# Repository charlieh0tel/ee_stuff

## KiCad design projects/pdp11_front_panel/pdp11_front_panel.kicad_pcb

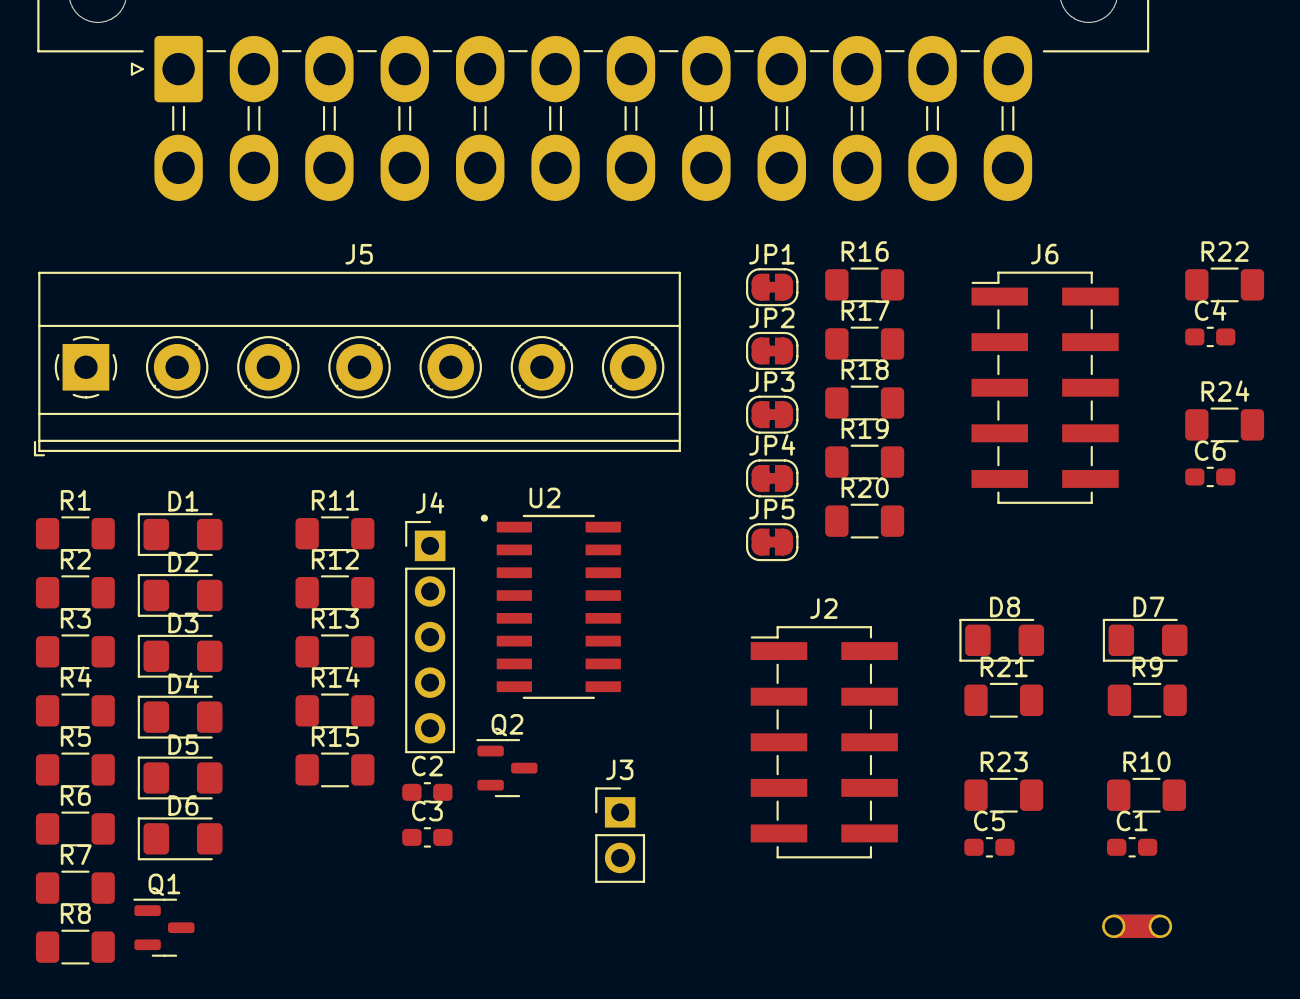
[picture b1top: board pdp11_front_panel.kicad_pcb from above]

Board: 2 copper layers, 53 parts (0 on the bottom side), 35 nets, no tracks yet.

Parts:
C1, C3, C4, C5, C6: 1u; C_0603_1608Metric_Pad1.08x0.95mm_HandSolder
C2: 0.01u; C_0603_1608Metric_Pad1.08x0.95mm_HandSolder
D1, D2, D3, D4, D5, D6, D7, D8: LED; LED_1206_3216Metric_Pad1.42x1.75mm_HandSolder
J1: ATX-24; Molex_Mini-Fit_Jr_5569-24A1_2x12_P4.20mm_Horizontal
J2, J6: Conn_02x05_Odd_Even; PinHeader_2x05_P2.54mm_Vertical_SMD
J3: Conn_01x02; PinHeader_1x02_P2.54mm_Vertical
J4: Conn_01x05_Pin; PinHeader_1x05_P2.54mm_Vertical
J5: Screw_Terminal_01x07; TerminalBlock_Phoenix_MKDS-1,5-7-5.08_1x07_P5.08mm_Horizont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
JP1, JP2, JP3, JP4, JP5: SolderJumper_2_Bridged; SolderJumper-2_P1.3mm_Bridged_RoundedPad1.0x1.5mm
NT1: NetTie_2; NetTie-2_THT_Pad1.0mm
Q1, Q2: 2N7002; SOT-23
R1, R12, R13, R14: 22; R_1206_3216Metric_Pad1.30x1.75mm_HandSolder
R2, R15: 100K; R_1206_3216Metric_Pad1.30x1.75mm_HandSolder
R3, R4, R5, R6, R7, R8: R; R_1206_3216Metric_Pad1.30x1.75mm_HandSolder
R9, R21: 1K; R_1206_3216Metric_Pad1.30x1.75mm_HandSolder
R10, R11, R22, R23, R24: 10K; R_1206_3216Metric_Pad1.30x1.75mm_HandSolder
R16, R17, R18, R19, R20: 2K; R_1206_3216Metric_Pad1.30x1.75mm_HandSolder
U2: AM26S10CDRG4; SOIC127P600X175-16N

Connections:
+5VA: C2.1, C3.1, NT1.2, R11.1, R16.2, R17.2, R18.2, R19.2, R20.2, U2.16 (VCC)
/+3V3: J1.1 (+3.3V), J1.2 (+3.3V), J1.12 (+3.3V), J1.13 (+3.3V), R7.1
/+5V: J1.4 (+5V), J1.6 (+5V), J1.21 (+5V), J1.22 (+5V), J1.23 (+5V), J5.1, J5.2, R8.1
/+5VSB: J1.9 (+5VSB), NT1.1, R3.1, R4.1
/+12V: J1.10 (+12V), J1.11 (+12V), J5.3, J5.4, R6.1
/-12V: J1.14 (-12V), J5.5, R5.1
/BDCOK_H: J2.10, J6.10, JP3.2 (B), U2.7 (2B)
/BEVNT_L: J2.2, J6.2, JP4.2 (B), U2.2 (1B)
/BHALT_L: J2.9, J6.9, JP2.2 (B), U2.9 (3B)
/BPOK_H: J2.1, J6.1, JP1.2 (B), U2.15 (4B)
/Controller/60HZ/50HZ#: J3.2, R11.2
/Controller/SW_AUX: C5.1, R23.2
/Controller/SW_PWR: C1.1, R10.2
/Controller/SW_RESTART#: C4.1, R22.2
/Controller/SW_RUN/HALT#: C6.1, R24.2
/PS_ON#: J1.16 (PS_ON#), Q2.3 (D)
/PWR_OK: J1.8 (PWR_OK), R1.1, R12.1
/SRUN_L: J2.3, J6.3, JP5.2 (B), R13.2
GND: C1.2, C2.2, C3.2, C4.2, C5.2, C6.2, D2.1 (K), D3.2 (A), D4.1 (K), D5.1 (K), D6.1 (K), D7.1 (K), D8.1 (K), J1.3 (GND), J1.5 (GND), J1.7 (GND), J1.15 (GND), J1.17 (GND), J1.18 (GND), J1.19 (GND), J1.24 (GND), J2.5, J3.1, J4.1, J5.6, J5.7, J6.5, Q1.2 (S), Q2.2 (S), R2.2, R15.2, U2.1 (GND), U2.8 (GND)
unnamed: D1.2 (A), R3.2
unnamed: D1.1 (K), Q1.3 (D)
unnamed: D2.2 (A), R4.2
unnamed: D3.1 (K), R5.2
unnamed: D4.2 (A), R6.2
unnamed: D5.2 (A), R7.2
unnamed: D6.2 (A), R8.2
unnamed: D7.2 (A), R9.2
unnamed: D8.2 (A), R21.2
unnamed: JP1.1 (A), R16.1
unnamed: JP2.1 (A), R17.1
unnamed: JP3.1 (A), R18.1
unnamed: JP4.1 (A), R19.1
unnamed: JP5.1 (A), R20.1
unnamed: Q1.1 (G), R1.2, R2.1
unnamed: Q2.1 (G), R14.2, R15.1

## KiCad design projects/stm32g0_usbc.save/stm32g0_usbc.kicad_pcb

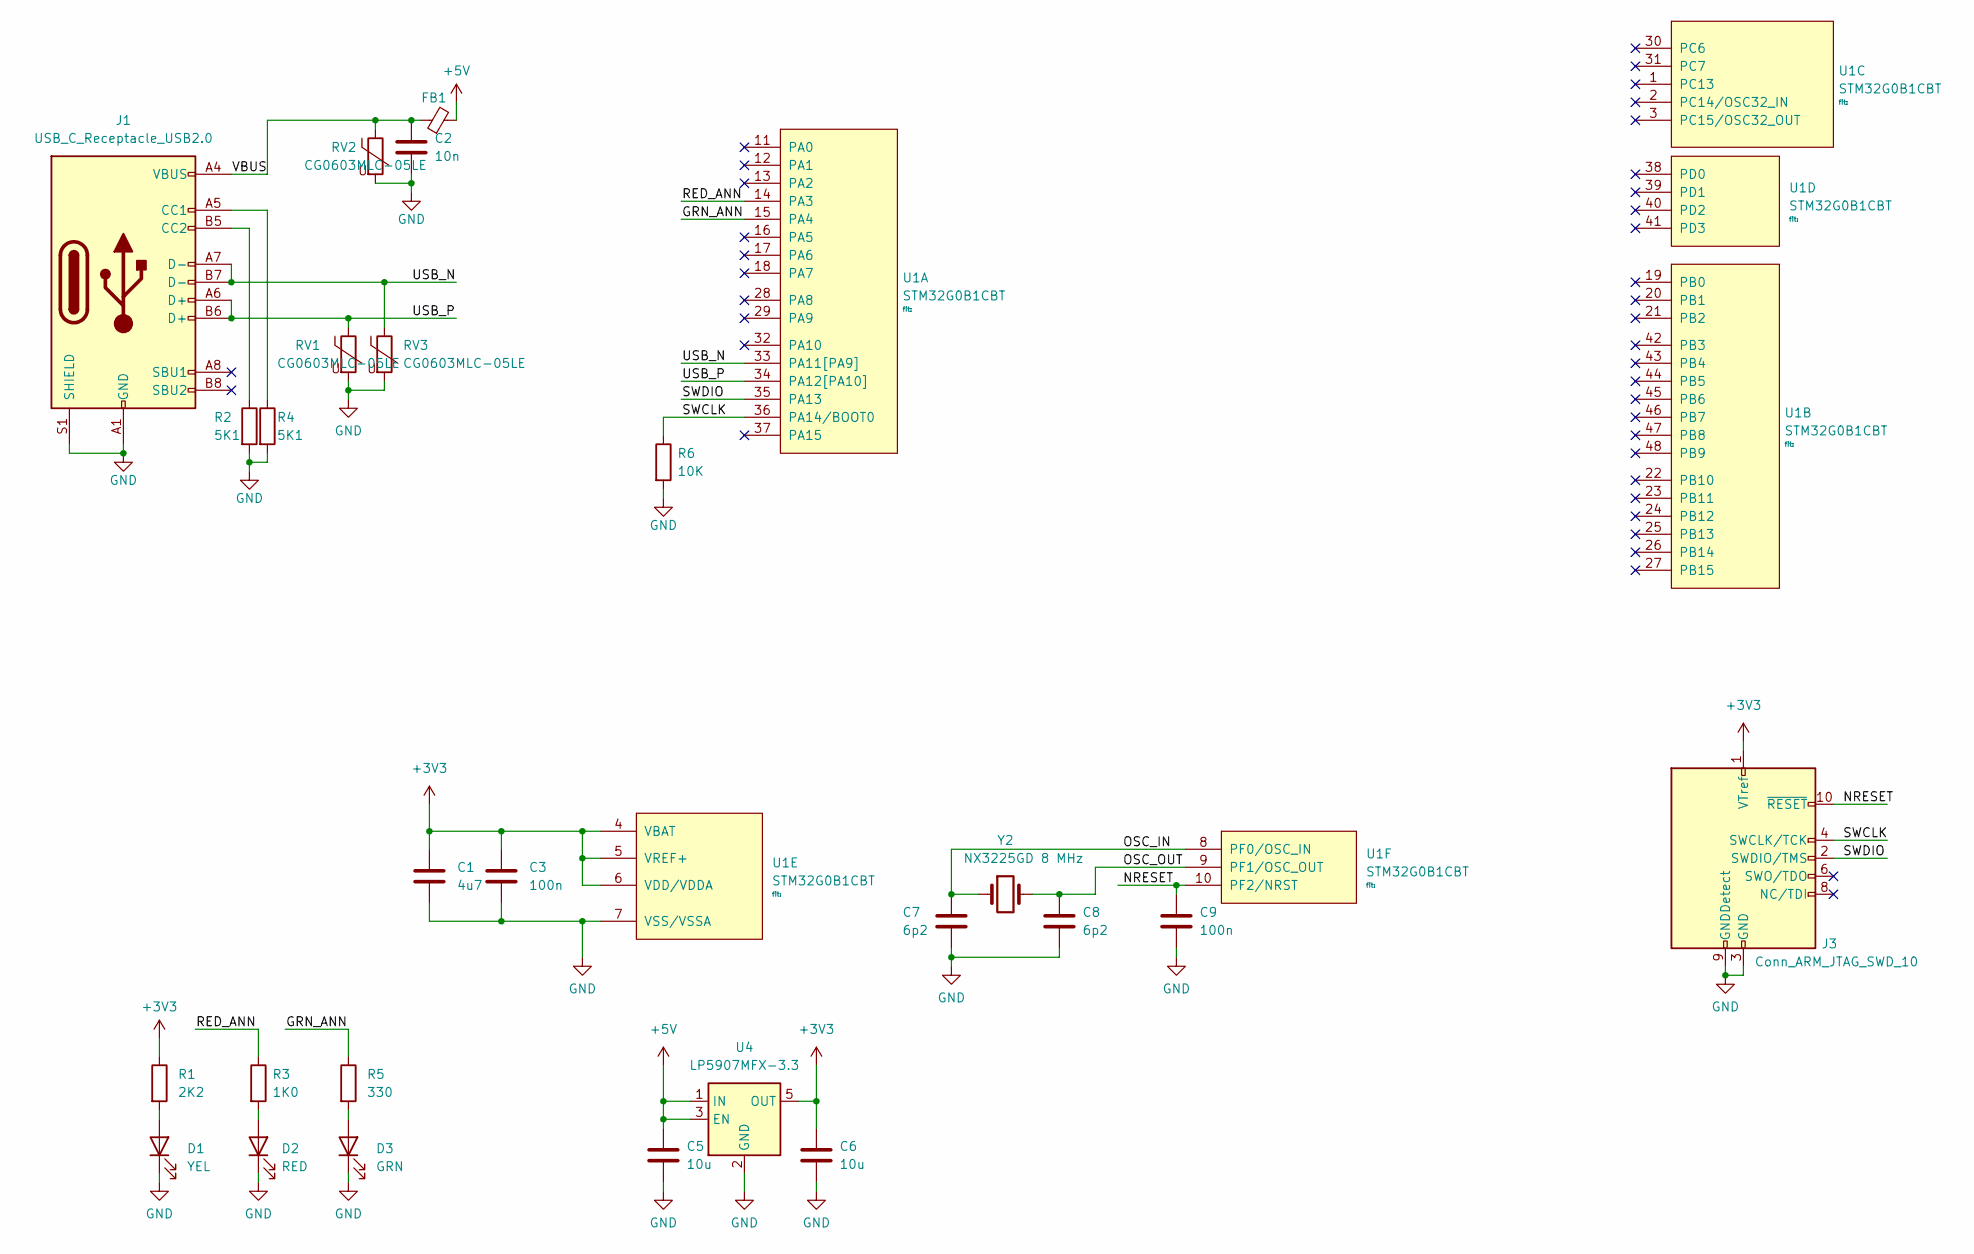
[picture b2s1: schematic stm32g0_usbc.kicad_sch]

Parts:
C1: 4u7; C_0603_1608Metric
C2: 10n; C_0603_1608Metric
C3, C9: 100n; C_0603_1608Metric
C5, C6: 10u; C_0805_2012Metric
C7, C8: 6p2; C_0402_1005Metric
D1: YEL; LED_0603_1608Metric
D2: RED; LED_0603_1608Metric
D3: GRN; LED_0603_1608Metric
FB1: FerriteBead_Small; D_0603_1608Metric_Pad1.05x0.95mm_HandSolder
J1: USB_C_Receptacle_USB2.0; USB_C_Receptacle_HCTL_HC-TYPE-C-16P-01A; LCSC C2997435
J3: Conn_ARM_JTAG_SWD_10; PinHeader_2x05_P1.27mm_Vertical
R1: 2K2; R_0603_1608Metric
R2, R4: 5K1; R_0603_1608Metric
R3: 1K0; R_0603_1608Metric
R5: 330; R_0603_1608Metric
R6: 10K; R_0603_1608Metric
RV1, RV2, RV3: CG0603MLC-05LE; R_0603_1608Metric; LCSC C2655331
U1: STM32G0B1CBT; LQFP-48_7x7mm_P0.5mm; MPN STM32G0B1CBT
U4: LP5907MFX-3.3; SOT-23-5
Y2: NX3225GD 8 MHz; Crystal_SMD_3215-2Pin_3.2x1.5mm; LCSC C889706

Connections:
+3V3: C1.1, C3.1, C6.1, J3.1 (VTref), R1.1, U1.4 (VBAT), U1.5 (VREF+), U1.6 (VDD/VDDA), U4.5 (OUT)
+5V: C5.1, FB1.2, U4.1 (IN), U4.3 (EN)
/GRN_ANN: R5.1, U1.15 (PA4)
/NRESET: C9.1, J3.10 (~RESET), U1.10 (PF2/NRST)
/OSC_IN: C7.1, U1.8 (PF0/OSC_IN), Y2.1
/OSC_OUT: C8.1, U1.9 (PF1/OSC_OUT), Y2.2
/RED_ANN: R3.1, U1.14 (PA3)
/SWCLK: J3.4 (SWCLK/TCK), R6.1, U1.36 (PA14/BOOT0)
/SWDIO: J3.2 (SWDIO/TMS), U1.35 (PA13)
/USB_N: J1.A7 (D-), J1.B7 (D-), RV3.1, U1.33 (PA11[PA9])
/USB_P: J1.A6 (D+), J1.B6 (D+), RV1.1, U1.34 (PA12[PA10])
/VBUS: C2.1, FB1.1, J1.A4 (VBUS), J1.A9 (VBUS), J1.B4 (VBUS), J1.B9 (VBUS), RV2.1
GND: C1.2, C2.2, C3.2, C5.2, C6.2, C7.2, C8.2, C9.2, D1.1 (K), D2.1 (K), D3.1 (K), J1.A1 (GND), J1.A12 (GND), J1.B1 (GND), J1.B12 (GND), J1.S1 (SHIELD), J3.3 (GND), J3.5 (GND), J3.9 (GNDDetect), R2.2, R4.2, R6.2, RV1.2, RV2.2, RV3.2, U1.7 (VSS/VSSA), U4.2 (GND)
unnamed: D1.2 (A), R1.2
unnamed: D2.2 (A), R3.2
unnamed: D3.2 (A), R5.2
unnamed: J1.A5 (CC1), R4.1
unnamed: J1.B5 (CC2), R2.1

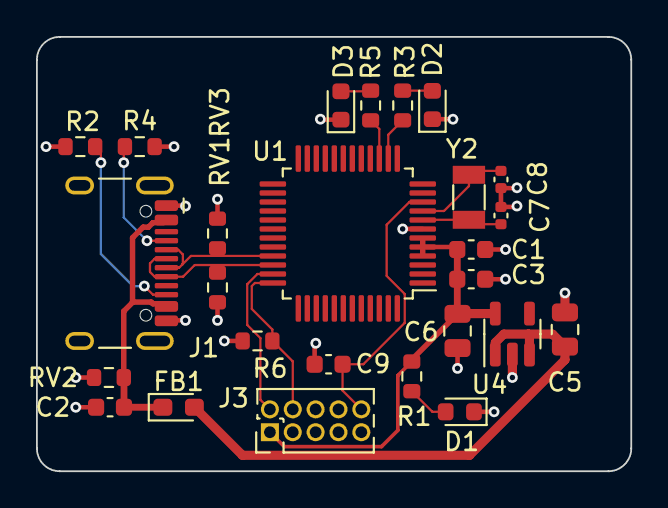
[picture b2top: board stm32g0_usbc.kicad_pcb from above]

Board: 2 copper layers, 33.0 x 24.1 mm, 26 parts (0 on the bottom side), 18 nets.
